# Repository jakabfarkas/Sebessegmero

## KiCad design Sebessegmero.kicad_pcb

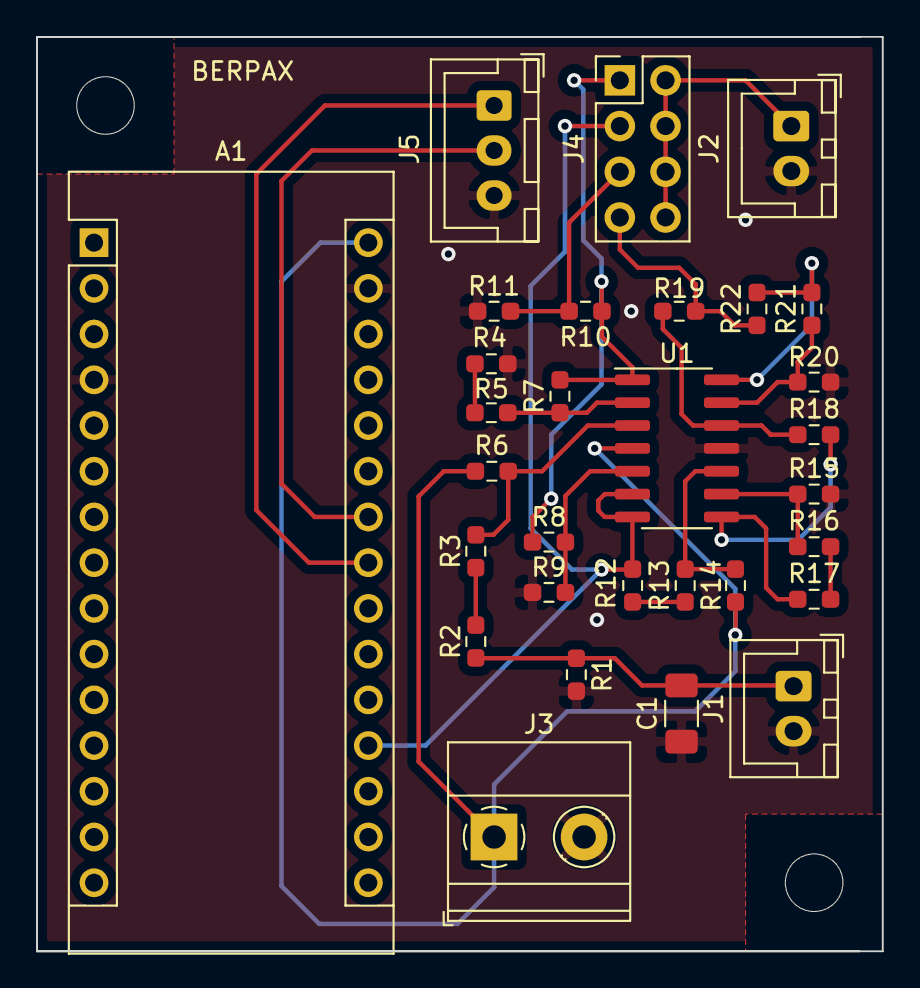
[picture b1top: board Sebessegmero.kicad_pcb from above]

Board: 2 copper layers, 47.0 x 50.8 mm, 30 parts (0 on the bottom side), 23 nets.

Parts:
A1: Arduino_Nano_Every; Arduino_Nano
C1: C; C_1206_3216Metric_Pad1.33x1.80mm_HandSolder
J1, J2: Conn_01x02_Female; JST_XH_B2B-XH-A_1x02_P2.50mm_Vertical
J3: Screw_Terminal_01x02; TerminalBlock_Phoenix_MKDS-1,5-2_1x02_P5.00mm_Horizontal
J4: Conn_02x04_Odd_Even; PinHeader_2x04_P2.54mm_Vertical
J5: Conn_01x03_Female; JST_XH_B3B-XH-A_1x03_P2.50mm_Vertical
R1, R7, R8, R9, R20: 10k; R_0603_1608Metric_Pad0.98x0.95mm_HandSolder
R2, R3: 3k; R_0603_1608Metric_Pad0.98x0.95mm_HandSolder
R4: 9,1k; R_0603_1608Metric_Pad0.98x0.95mm_HandSolder
R5: 130; R_0603_1608Metric_Pad0.98x0.95mm_HandSolder
R6, R14, R15: 24k; R_0603_1608Metric_Pad0.98x0.95mm_HandSolder
R10: 2k; R_0603_1608Metric_Pad0.98x0.95mm_HandSolder
R11: 1k; R_0603_1608Metric_Pad0.98x0.95mm_HandSolder
R12, R16: 2,4k; R_0603_1608Metric_Pad0.98x0.95mm_HandSolder
R13, R17: 100; R_0603_1608Metric_Pad0.98x0.95mm_HandSolder
R18: 100k; R_0603_1608Metric_Pad0.98x0.95mm_HandSolder
R19, R21: 15k; R_0603_1608Metric_Pad0.98x0.95mm_HandSolder
R22: 47; R_0603_1608Metric_Pad0.98x0.95mm_HandSolder
U1: Opamp_Quad_Generic; SOIC-14_3.9x8.7mm_P1.27mm

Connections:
0-3V3: J4.5, R10.2, R11.1
0-5V: A1.19, J4.3, R12.1, U1.6, U1.7
0-10V: J4.1, R7.2, R8.1, R10.1, U1.1
4-20mA: J4.7, R19.1, R22.1
+12V: A1.30, J3.1, R6.1, R14.2, U1.4
GND: A1.4, A1.29, C1.2, J1.2, J2.2, J3.2, J5.3, R1.2, R4.1, R9.2, R11.2, R15.2, R20.1, U1.11
unnamed: A1.23, J5.1
unnamed: A1.24, J5.2
unnamed: C1.1, J1.1, R1.1, R2.2
unnamed: J2.1, J4.2, J4.4, J4.6, J4.8
unnamed: R2.1, R3.2
unnamed: R3.1, R6.2, U1.3
unnamed: R4.2, R5.1
unnamed: R5.2, R7.1, U1.2
unnamed: R8.2, R9.1, U1.5
unnamed: R12.2, R13.1
unnamed: R13.2, R14.1, U1.10
unnamed: R15.1, R16.1, U1.9
unnamed: R16.2, R17.2
unnamed: R17.1, R18.2, U1.8
unnamed: R18.1, R19.2, U1.12
unnamed: R20.2, R21.1, U1.13
unnamed: R21.2, R22.2, U1.14

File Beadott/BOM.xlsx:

Description | Value | Quantity | References | Link
Arduino Nano |  | 1 | A1 | https://content.arduino.cc/assets/NANOEveryV3.0_sch.pdf
Quad operational amplifier |  | 1 | U1 | https://hu.farnell.com/on-semiconductor/mc33204dr2g/op-amp-2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
JST connector, 01x02 |  | 2 | J1, J2 | https://www.digikey.hu/product-detail/en/jst-sales-america-i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
Screw terminal, 01x02 |  | 1 | J3 | https://hu.farnell.com/buchanan-te-connectivity/282837-2/ter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
Pin Header, 02x04 |  | 1 | J4 | https://hu.farnell.com/molex/87758-0816/connector-header-8po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
JST connector, 01x03 |  | 1 | J5 | https://www.digikey.hu/product-detail/en/jst-sales-america-i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
Unpolarized capacitor | 10uF | 1 | C1 | https://hu.farnell.com/avx/1206yc106kat2a/cap-10-f-16v-10-x7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
Resistor | 10k | 5 | R1, R7, R8, R9, R20 | https://hu.farnell.com/yageo/ac0603fr-0710kl/res-10k-1-0-1w-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
Resistor | 3k | 2 | R2, R3 | https://hu.farnell.com/vishay/crcw06033k00fkea/res-3k-1-0-1w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
Resistor | 9,1k | 1 | R4 | https://hu.farnell.com/vishay/crcw06039k10fkea/res-9k1-1-0-1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
Resistor | 130 | 1 | R5 | https://hu.farnell.com/multicomp/mcwr06x1300ftl/res-130r-1-0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
Resistor | 24k | 3 | R6, R14, R15 | https://hu.farnell.com/multicomp/mcwr06x2402ftl/res-24k-1-0-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
Resistor | 2k | 1 | R10 | https://hu.farnell.com/vishay/crcw06032k00fkea/res-2k-1-0-1w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
Resistor | 1k | 1 | R11 | https://hu.farnell.com/yageo/ac0603fr-071kl/res-1k-1-0-1w-06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
Resistor | 2,4k | 2 | R12, R16 | https://hu.farnell.com/multicomp/mcwr06x2401ftl/res-2k4-1-0-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
Resistor | 100 | 2 | R13, R17 | https://hu.farnell.com/yageo/ac0603fr-07100rl/res-100r-1-0-1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
Resistor | 100k | 1 | R18 | https://hu.farnell.com/vishay/crcw0603100kfkea/res-100k-1-0-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
Resistor | 15k | 2 | R19, R21 | https://hu.farnell.com/vishay/crcw060315k0fkea/res-15k-1-0-1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
Resistor | 47 | 1 | R22 | https://hu.farnell.com/vishay/crcw060347r0fkeahp/res-47r-1-0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

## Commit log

2020-11-27 ellenallas linkek
2020-11-27 csatlakozo linkek
2020-11-28 footprintek
2020-11-28 extra step fajlok
2020-11-28 nano step torles
2020-12-02 footprint_elotti
2020-12-02 Footprint by Zsombi
2020-12-02 farkas layoutja
2020-12-02 farkas layout
2020-12-12 kesz aramkor
2020-12-12 Készkörüli doksi
2020-12-12 Szimuláció
2020-12-12 doksi 3.0
2020-12-13 Kész doksi
2020-12-13 Leadva
